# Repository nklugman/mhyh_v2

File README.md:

An artifical heart simulator written in both processing and arduino for Project
My Heart Your Heart.

Flash the firmware onto a Due board and run the processing.

The processing has debug and advanced flags. Comments are in code for now.

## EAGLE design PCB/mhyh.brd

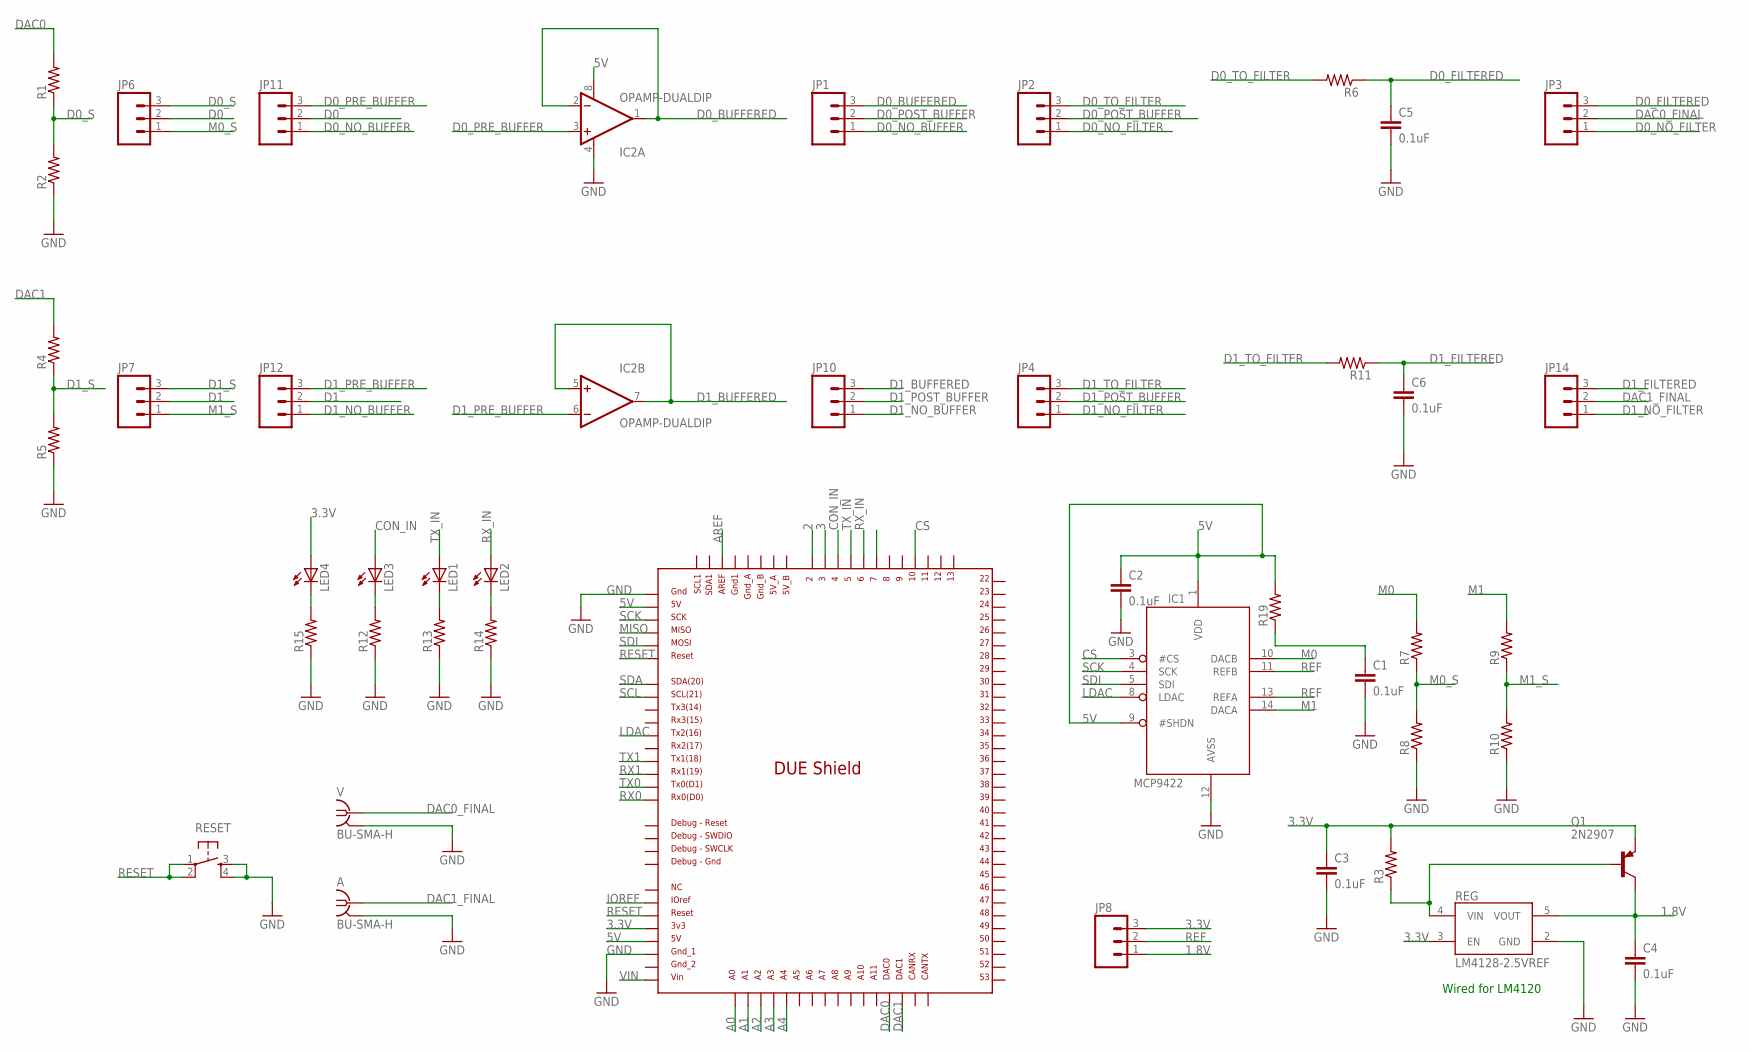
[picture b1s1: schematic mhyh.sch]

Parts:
A: BU-SMA-H
C1, C2, C3, C4, C5, C6: 0.1uF; 0603-CAP
IC1: MCP9422; DIL14
IC2: OPAMP-DUALDIP; DIP08
JP1, JP2, JP3, JP4, JP6, JP7, JP8, JP10, JP11, JP12, JP14: M03LOCK; 1X03_LOCK
LED1, LED2, LED3, LED4: LEDCHIPLED_0603; CHIPLED_0603
Q1: 2N2907; TO92-EBC-OVAL
R1, R2, R3, R4, R5, R6, R7, R8, R9, R10, R11, R12, R13, R14, R15, R19: RESISTOR0603-RES; 0603-RES
REG: LM4128-2.5VREF; SOT23-5
RESET: TAC_SWITCHPTH; TACTILE-PTH
U$1: DUE(NORMAL)
V: BU-SMA-H

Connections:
1.8V: C4.1, JP8.1, Q1.C, REG.5 (VOUT)
2: U$1.2
3: U$1.3
3.3V: C3.1, JP8.3, LED4.A, Q1.E, R3.2, REG.3 (EN), U$1.3V3
5V: C2.1, IC1.1 (VDD), IC1.9 (#SHDN), IC2.8 (V+), R19.2, U$1.5V, U$1.GND_ICSP
A0: U$1.A0
A1: U$1.A1
A2: U$1.A2
A3: U$1.A3
A4: U$1.A4
AREF: U$1.AREF
CON_IN: LED3.A, U$1.4
CS: IC1.3 (#CS), U$1.10
D0: JP6.2, JP11.2
D0_BUFFERED: IC2.1 (OUT), IC2.2 (-IN), JP1.3
D0_FILTERED: C5.1, JP3.3, R6.1
D0_NO_BUFFER: JP1.1, JP11.1
D0_NO_FILTER: JP2.1, JP3.1
D0_POST_BUFFER: JP1.2, JP2.2
D0_PRE_BUFFER: IC2.3 (+IN), JP11.3
D0_S: JP6.3, R1.1, R2.2
D0_TO_FILTER: JP2.3, R6.2
D1: JP7.2, JP12.2
D1_BUFFERED: IC2.5 (+IN), IC2.7 (OUT), JP10.3
D1_FILTERED: C6.1, JP14.3, R11.1
D1_NO_BUFFER: JP10.1, JP12.1
D1_NO_FILTER: JP4.1, JP14.1
D1_POST_BUFFER: JP4.2, JP10.2
D1_PRE_BUFFER: IC2.6 (-IN), JP12.3
D1_S: JP7.3, R4.1, R5.2
D1_TO_FILTER: JP4.3, R11.2
DAC0: R1.2, U$1.DAC0
DAC0_FINAL: JP3.2, V.1
DAC1: R4.2, U$1.DAC1
DAC1_FINAL: A.1, JP14.2
GND: A.2, A.3 (2), A.4 (2), A.5 (2), C1.2, C2.2, C3.2, C4.2, C5.2, C6.2, IC1.12 (AVSS), IC2.4 (V-), R2.1, R5.1, R8.1, R10.1, R12.1, R13.1, R14.1, R15.1, REG.2 (GND), RESET.3, RESET.4, U$1.5V_ICSP, U$1.GND_1, V.2, V.3 (2), V.4 (2), V.5 (2)
IOREF: U$1.IOREF
LDAC: IC1.8 (LDAC), U$1.TX2
M0: IC1.10 (DACB), R7.2
M0_S: JP6.1, R7.1, R8.2
M1: IC1.14 (DACA), R9.2
M1_S: JP7.1, R9.1, R10.2
MISO: U$1.MISO_ICSP
unnamed: Q1.B, R3.1, REG.4 (VIN)
unnamed: C1.1, R19.1
unnamed: LED1.C, R13.2
unnamed: LED2.C, R14.2
unnamed: LED4.C, R15.2
unnamed: LED3.C, R12.2
REF: IC1.11 (REFB), IC1.13 (REFA), JP8.2
RESET: RESET.1, RESET.2, U$1.RESET, U$1.RESET_ICSP
RX0: U$1.RX0
RX1: U$1.RX1
RX_IN: LED2.A, U$1.6
SCK: IC1.4 (SCK), U$1.SCK_ICSP
SCL: U$1.SCL
SDA: U$1.SDA
SDI: IC1.5 (SDI), U$1.MOSI_ICSP
SHDN: U$1.7
TX0: U$1.TX0
TX1: U$1.TX1
TX_IN: LED1.A, U$1.5
VIN: U$1.VIN

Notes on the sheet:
Wired for LM4120

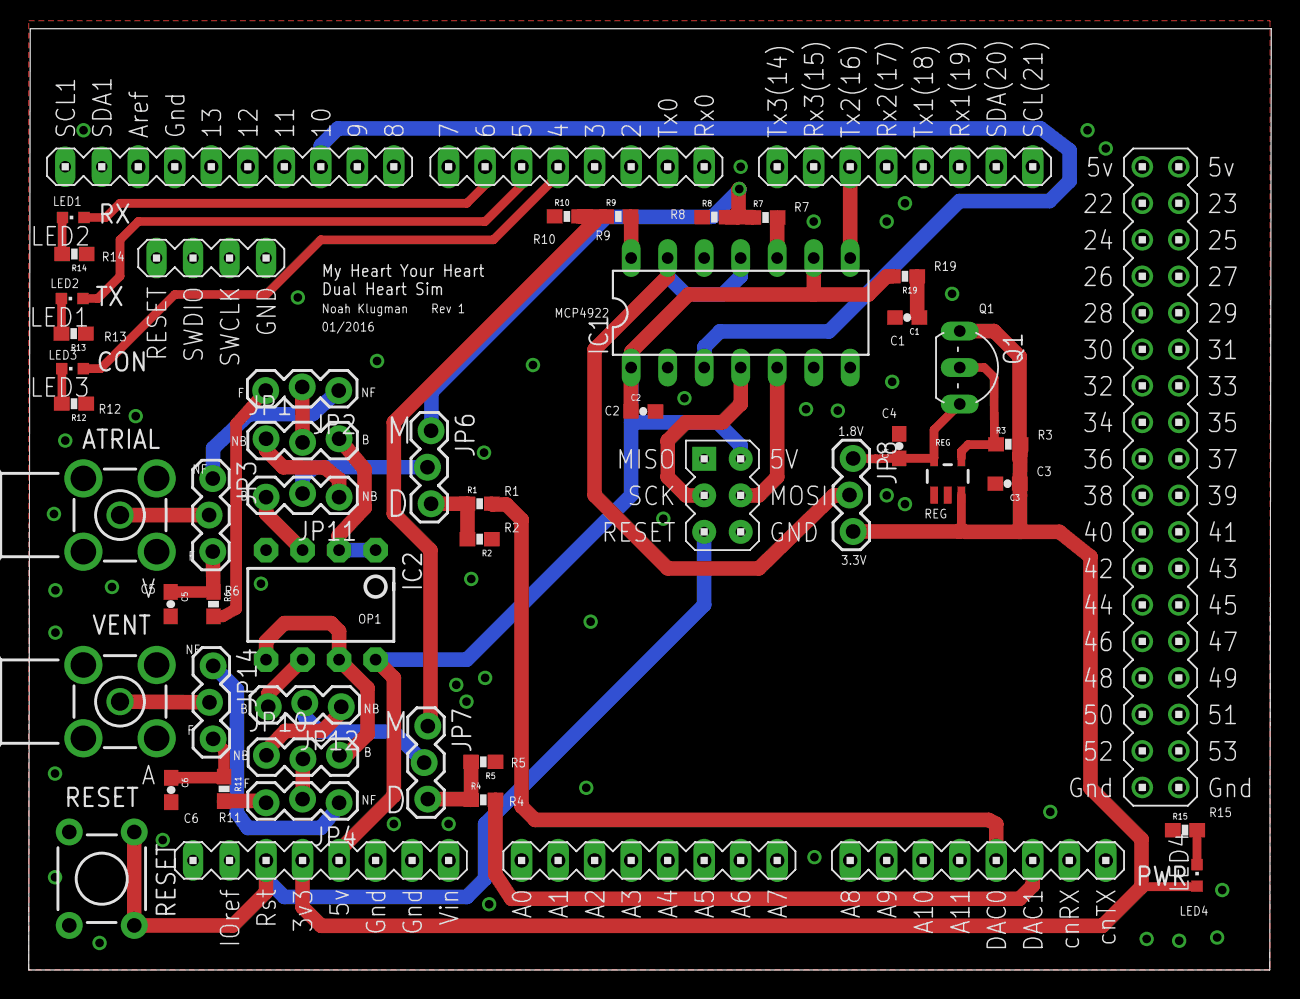
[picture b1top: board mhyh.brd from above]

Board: 2 copper layers, 86.4 x 65.5 mm, 45 parts (0 on the bottom side), 45 nets.

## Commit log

2014-09-09 inital commit... adding in the files
2014-09-09 readme
2015-02-04 significant changes to GUI. Test Suite implementented but not well tested
2016-01-19 adding in pcb and gerbers
2016-03-12 new arduino
2016-03-12 new mhyh processing
2016-03-15 adding in spi dac
2016-03-16 cur versions

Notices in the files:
parts and their libraries:
SparkFun-Electromechanical: Licensing: Creative Commons ShareAlike 4.0 International - https://creativecommons.org/licenses/by-sa/4.0
